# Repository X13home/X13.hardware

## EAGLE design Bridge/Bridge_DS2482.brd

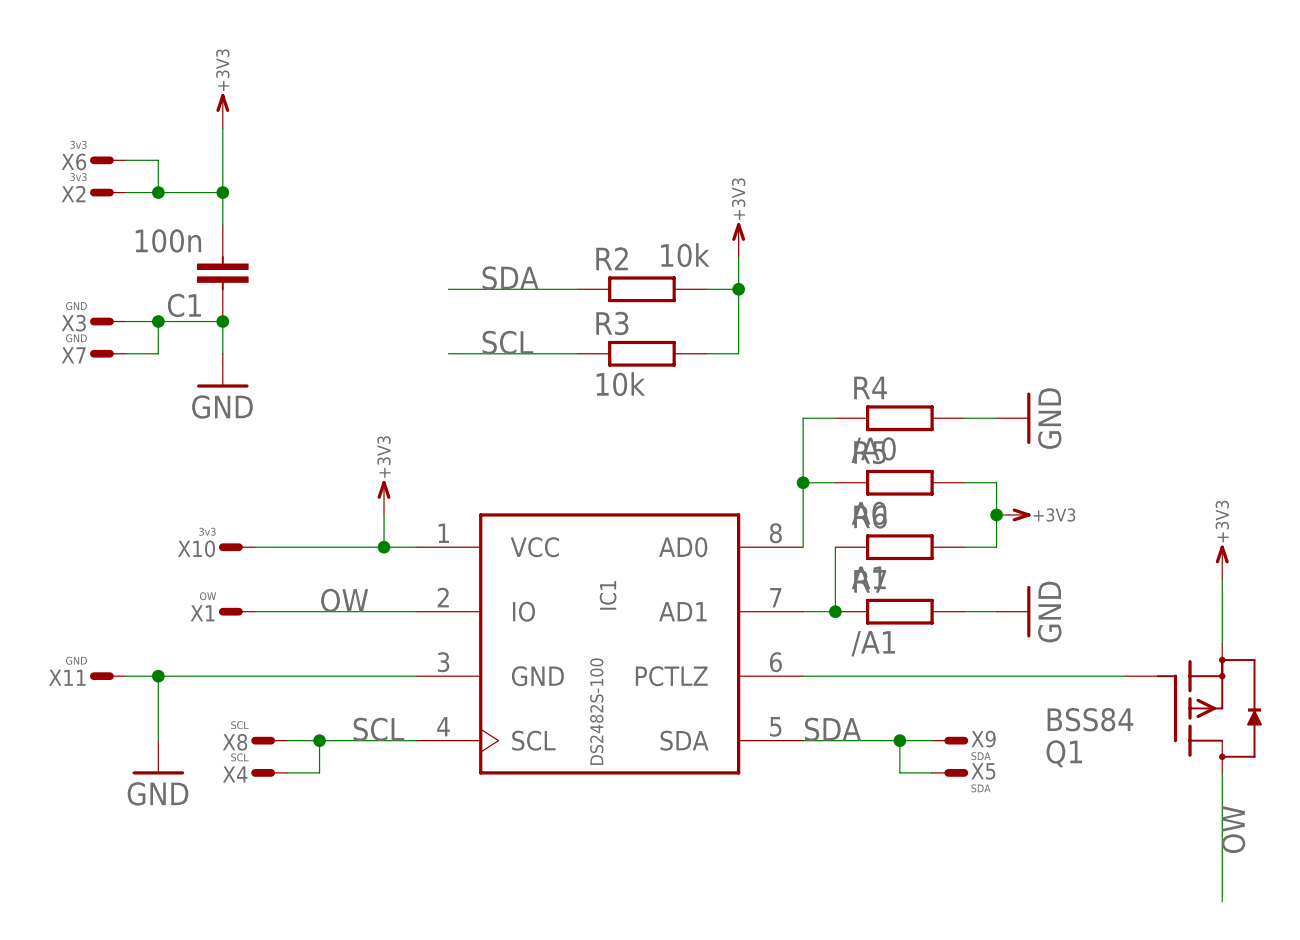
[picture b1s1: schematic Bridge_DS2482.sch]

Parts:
C1: 100n; 0603
IC1: DS2482S-100; SO8
Q1: BSS84; SOT23
R2, R3: 10k; 0603
R4: /A0; 0603
R5: A0; 0603
R6: A1; 0603
R7: /A1; 0603
X1: OW; T1.6/0.9
X2, X6, X10: 3v3; T1.6/0.9
X3, X7, X11: GND; T1.6/0.9
X4, X8: SCL; T1.6/0.9
X5, X9: SDA; T1.6/0.9

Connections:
+3V3: C1.2, IC1.1 (VCC), Q1.2 (S), R2.2, R3.2, R5.2, R6.2, X2.1, X6.1, X10.1
GND: C1.1, IC1.3 (GND), R4.2, R7.2, X3.1, X7.1, X11.1
unnamed: IC1.7 (AD1), R6.1, R7.1
unnamed: IC1.8 (AD0), R4.1, R5.1
unnamed: IC1.6 (PCTLZ), Q1.1 (G)
OW: IC1.2 (IO), Q1.3 (D), X1.1
SCL: IC1.4 (SCL), R3.1, X4.1, X8.1
SDA: IC1.5 (SDA), R2.1, X5.1, X9.1

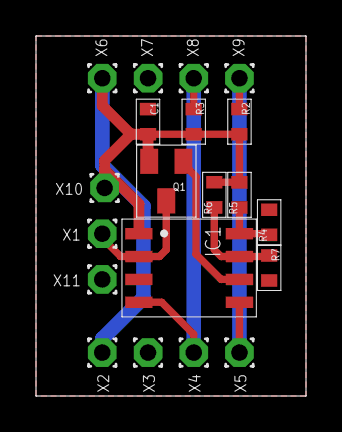
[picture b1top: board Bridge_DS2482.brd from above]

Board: 2 copper layers, 15.0 x 20.0 mm, 20 parts (0 on the bottom side), 8 nets.

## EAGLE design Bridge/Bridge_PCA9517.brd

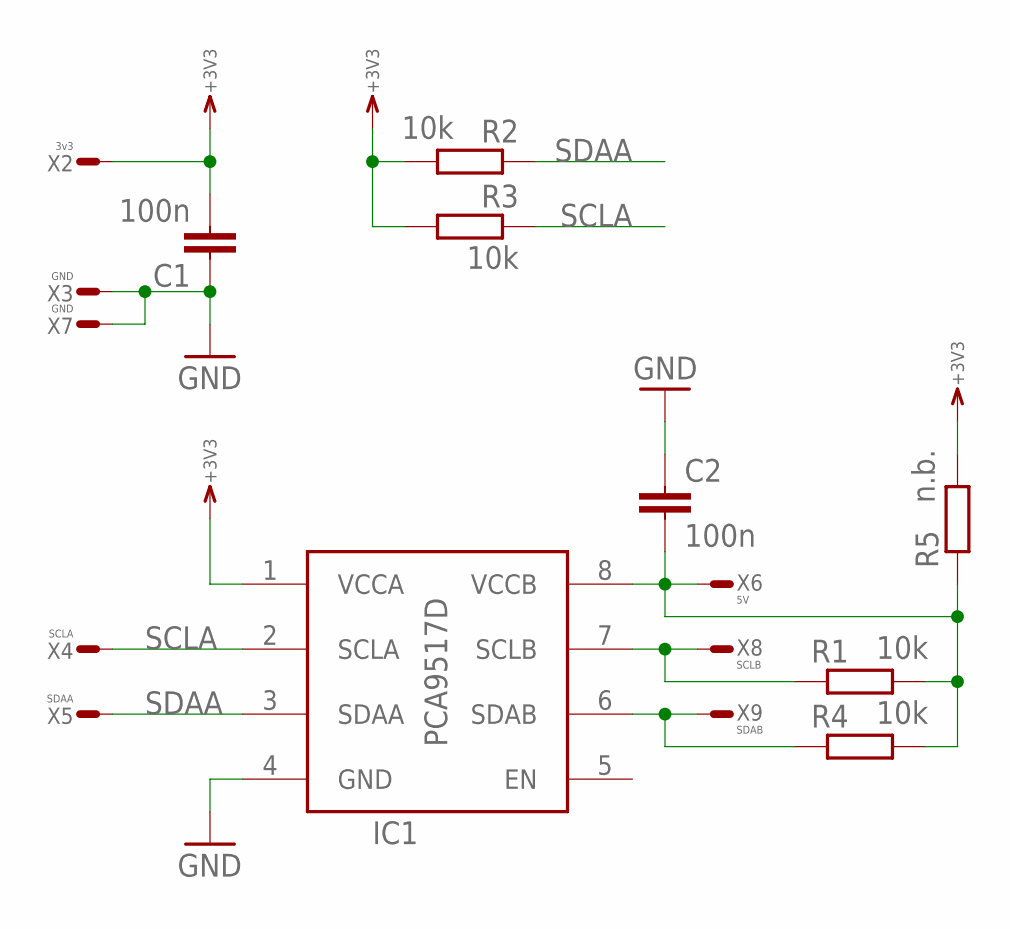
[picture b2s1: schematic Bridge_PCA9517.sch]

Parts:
C1, C2: 100n; 0603
IC1: PCA9517D; SOIC8
R1, R2, R3, R4: 10k; 0603
R5: n.b.; 0603
X2: 3v3; T1.6/0.9
X3, X7: GND; T1.6/0.9
X4: SCLA; T1.6/0.9
X5: SDAA; T1.6/0.9
X6: 5V; T1.6/0.9
X8: SCLB; T1.6/0.9
X9: SDAB; T1.6/0.9

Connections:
+3V3: C1.2, IC1.1 (VCCA), R2.2, R3.2, R5.2, X2.1
GND: C1.1, C2.1, IC1.4 (GND), X3.1, X7.1
unnamed: C2.2, IC1.8 (VCCB), R1.2, R4.2, R5.1, X6.1
SCLA: IC1.2 (SCLA), R3.1, X4.1
SCLB: IC1.7 (SCLB), R1.1, X8.1
SDAA: IC1.3 (SDAA), R2.1, X5.1
SDAB: IC1.6 (SDAB), R4.1, X9.1

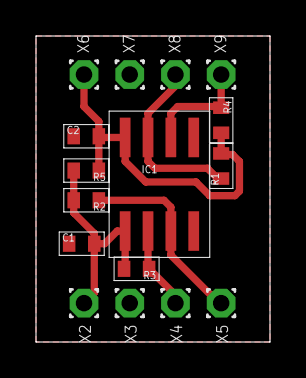
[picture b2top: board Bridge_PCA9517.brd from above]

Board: 2 copper layers, 13.0 x 17.0 mm, 16 parts (0 on the bottom side), 7 nets.

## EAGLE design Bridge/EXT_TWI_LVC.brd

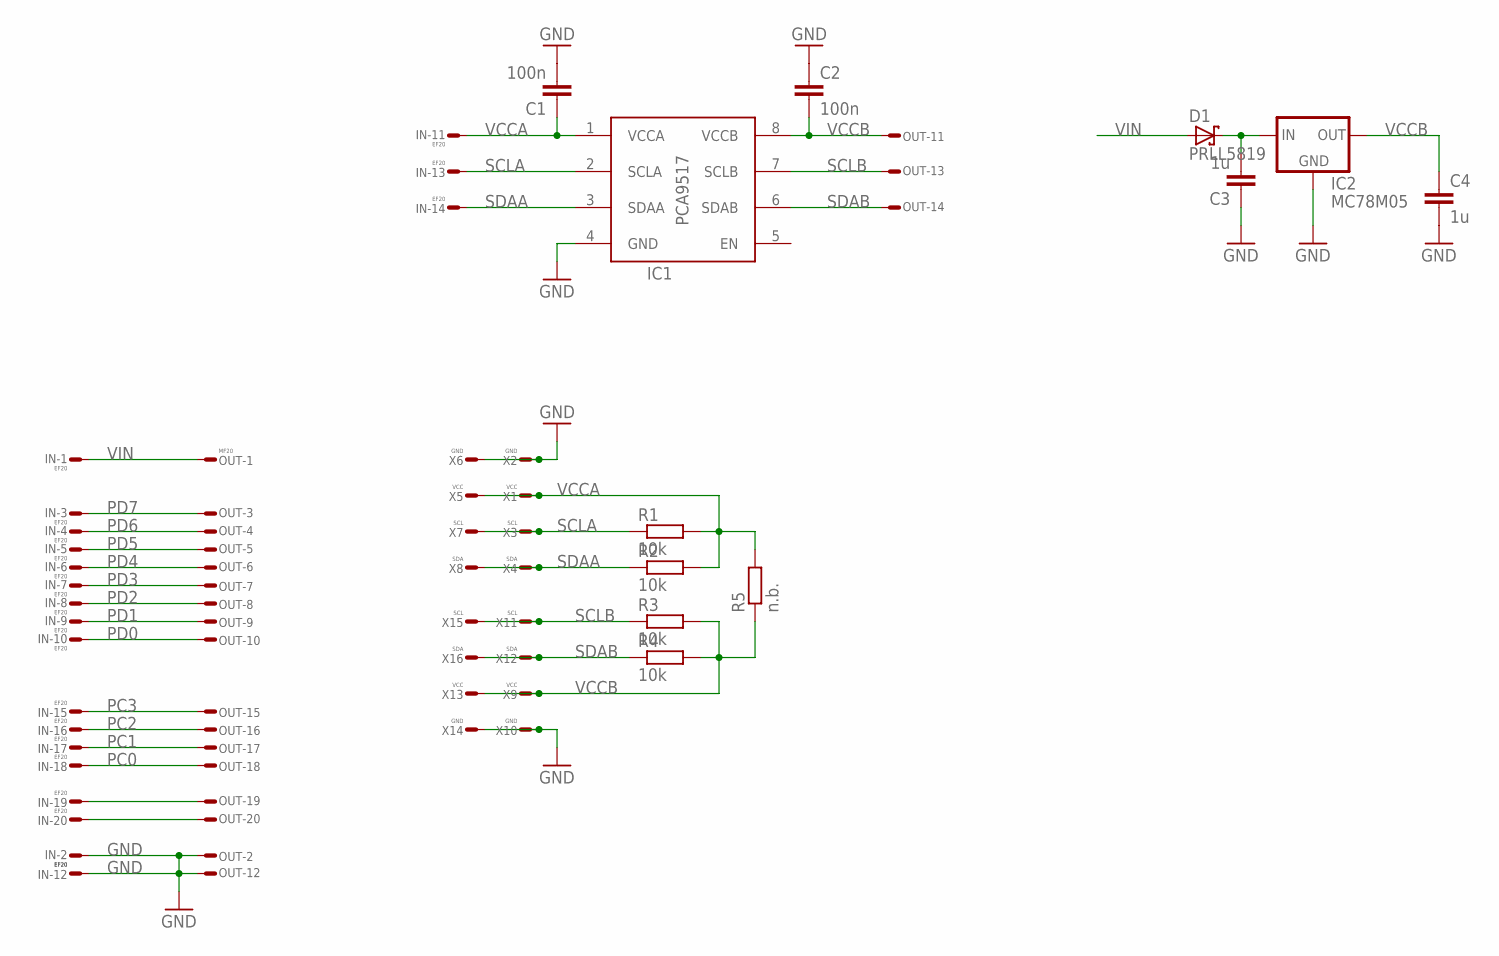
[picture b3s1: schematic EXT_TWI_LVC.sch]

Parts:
C1, C2: 100n; 0603
C3, C4: 1u; 1206
D1: PRLL5819; SOD87
IC1: PCA9517; SOIC8
IC2: MC78M05; DPAK
IN: EF20; FE10-2WSS
OUT: MF20; ML20LS
R1, R2, R3, R4: 10k; 0603
R5: n.b.; 1206
X1, X5, X9, X13: VCC; T1.6/0.9
X2, X6, X10, X14: GND; T1.6/0.9
X3, X7, X11, X15: SCL; T1.6/0.9
X4, X8, X12, X16: SDA; T1.6/0.9

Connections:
GND: C1.2, C2.1, C3.1, C4.2, IC1.4 (GND), IC2.4 (GND), IN.P$2, IN.P$12, OUT.P$2, OUT.P$12, X2.1, X6.1, X10.1, X14.1
unnamed: IN.P$20, OUT.P$20
unnamed: C3.2, D1.C, IC2.1 (IN)
unnamed: IN.P$19, OUT.P$19
PC0: IN.P$18, OUT.P$18
PC1: IN.P$17, OUT.P$17
PC2: IN.P$16, OUT.P$16
PC3: IN.P$15, OUT.P$15
PD0: IN.P$10, OUT.P$10
PD1: IN.P$9, OUT.P$9
PD2: IN.P$8, OUT.P$8
PD3: IN.P$7, OUT.P$7
PD4: IN.P$6, OUT.P$6
PD5: IN.P$5, OUT.P$5
PD6: IN.P$4, OUT.P$4
PD7: IN.P$3, OUT.P$3
SCLA: IC1.2 (SCLA), IN.P$13, R1.1, X3.1, X7.1
SCLB: IC1.7 (SCLB), OUT.P$13, R3.1, X11.1, X15.1
SDAA: IC1.3 (SDAA), IN.P$14, R2.1, X4.1, X8.1
SDAB: IC1.6 (SDAB), OUT.P$14, R4.1, X12.1, X16.1
VCCA: C1.1, IC1.1 (VCCA), IN.P$11, R1.2, R2.2, R5.2, X1.1, X5.1
VCCB: C2.2, C4.1, IC1.8 (VCCB), IC2.3 (OUT), OUT.P$11, R3.2, R4.2, R5.1, X9.1, X13.1
VIN: D1.A, IN.P$1, OUT.P$1

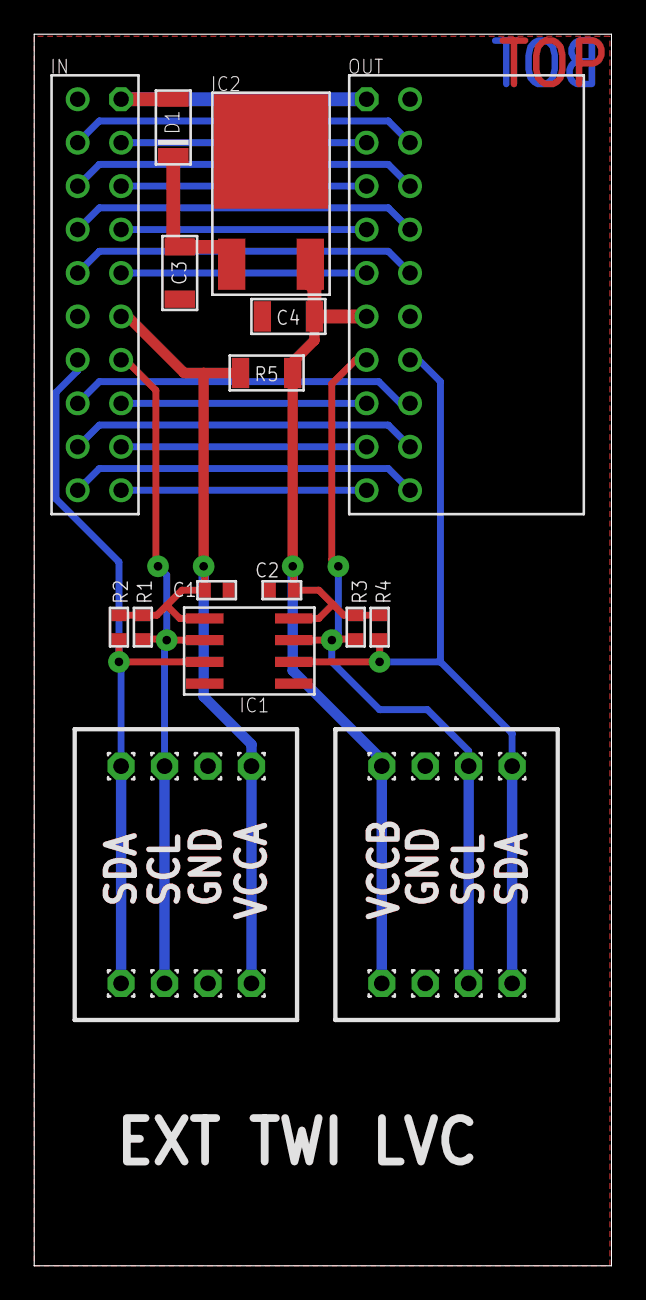
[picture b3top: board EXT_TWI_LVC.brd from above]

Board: 2 copper layers, 33.8 x 72.0 mm, 30 parts (0 on the bottom side), 23 nets.

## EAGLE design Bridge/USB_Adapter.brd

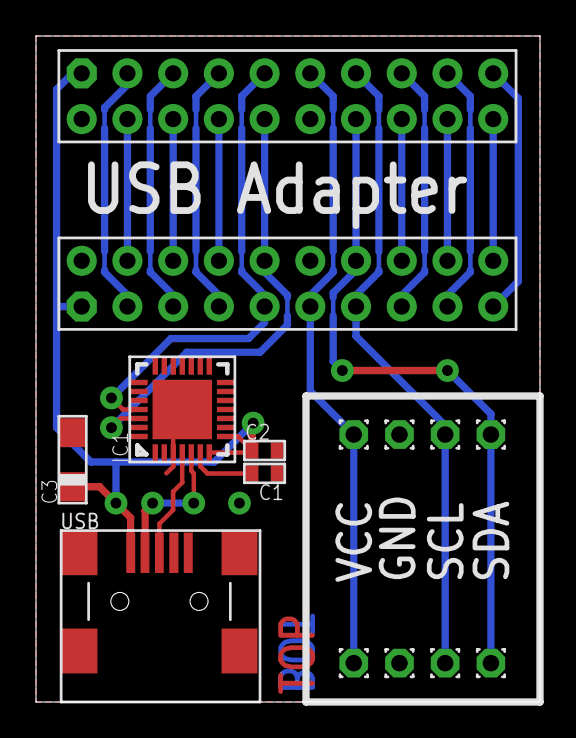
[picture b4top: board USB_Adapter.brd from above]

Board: 4 copper layers, 28.0 x 37.0 mm, 15 parts (1 on the bottom side), 22 nets.

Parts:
C1: 100n; 0603
C2: 1u; 0603
C3: 4u7; SMC_A
IC1: QFN28
OUT: MF20; ML20S
TRV: ML20S
USB: USB-BM
X1, X3, X4, X5, X6, X7, X8, X9: T1.6/0.9

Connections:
+3V3: OUT.11, TRV.11, X1.1, X6.1
GND: C1.1, C2.2, C3.-, IC1.3, IC1.P, OUT.2, OUT.12, TRV.2, TRV.12, USB.5, X3.1, X7.1
unnamed: OUT.20, TRV.20
unnamed: C1.2, IC1.6
unnamed: OUT.19, TRV.19
unnamed: IC1.4, USB.3
unnamed: IC1.5, USB.2
PC0: OUT.18, TRV.18
PC1: OUT.17, TRV.17
PC2: OUT.16, TRV.16
PC3: OUT.15, TRV.15
PC4/SDA: OUT.14, TRV.14, X5.1, X9.1
PC5/SCL: OUT.13, TRV.13, X4.1, X8.1
PD0: IC1.26, OUT.10, TRV.10
PD1: IC1.25, OUT.9, TRV.9
PD2: OUT.8, TRV.8
PD3: OUT.7, TRV.7
PD4: OUT.6, TRV.6
PD5: OUT.5, TRV.5
PD6: OUT.4, TRV.4
PD7: OUT.3, TRV.3
VIN: C2.1, C3.+, IC1.7, IC1.8, OUT.1, TRV.1, USB.1

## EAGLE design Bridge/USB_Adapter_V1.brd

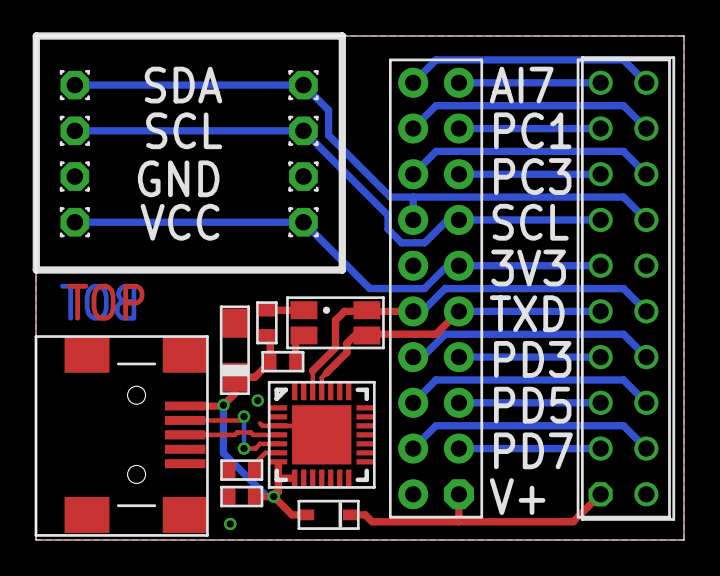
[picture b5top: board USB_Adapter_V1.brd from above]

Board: 2 copper layers, 36.0 x 28.0 mm, 19 parts (0 on the bottom side), 25 nets.

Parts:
C1: 100n; 0603
C2: 1u; 0603
C3: 4u7; SMC_A
D1: SOD323
IC1: CP2102; QFN28
LED1: HSMF
R1, R2: 1K; 0603
SV1: TRV; FE10-2WSS
SV2: ML20S
USB: USB; USB-BM
X1, X3, X4, X5, X6, X7, X8, X9: T1.6/0.9

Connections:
+3V3: SV1.P$11, SV2.11, X1.1, X6.1
AI6: SV1.P$20, SV2.20
AI7: SV1.P$19, SV2.19
GND: C1.1, C2.2, C3.-, IC1.3, IC1.P, SV1.P$2, SV1.P$12, SV2.2, SV2.12, USB.5, X3.1, X7.1
unnamed: D1.C, SV1.P$1, SV2.1
unnamed: C1.2, IC1.6
unnamed: LED1.3, R1.1
unnamed: IC1.4, USB.3
unnamed: LED1.1, R2.1
unnamed: IC1.5, USB.2
PC0: SV1.P$18, SV2.18
PC1: SV1.P$17, SV2.17
PC2: SV1.P$16, SV2.16
PC3: SV1.P$15, SV2.15
PC4/SDA: SV1.P$14, SV2.14, X5.1, X9.1
PC5/SCL: SV1.P$13, SV2.13, X4.1, X8.1
PD0: IC1.26, LED1.2, SV1.P$10, SV2.10
PD1: IC1.25, LED1.4, SV1.P$9, SV2.9
PD2: SV1.P$8, SV2.8
PD3: SV1.P$7, SV2.7
PD4: SV1.P$6, SV2.6
PD5: SV1.P$5, SV2.5
PD6: SV1.P$4, SV2.4
PD7: SV1.P$3, SV2.3
VIN: C2.1, C3.+, D1.A, IC1.7, IC1.8, R1.2, R2.2, USB.1

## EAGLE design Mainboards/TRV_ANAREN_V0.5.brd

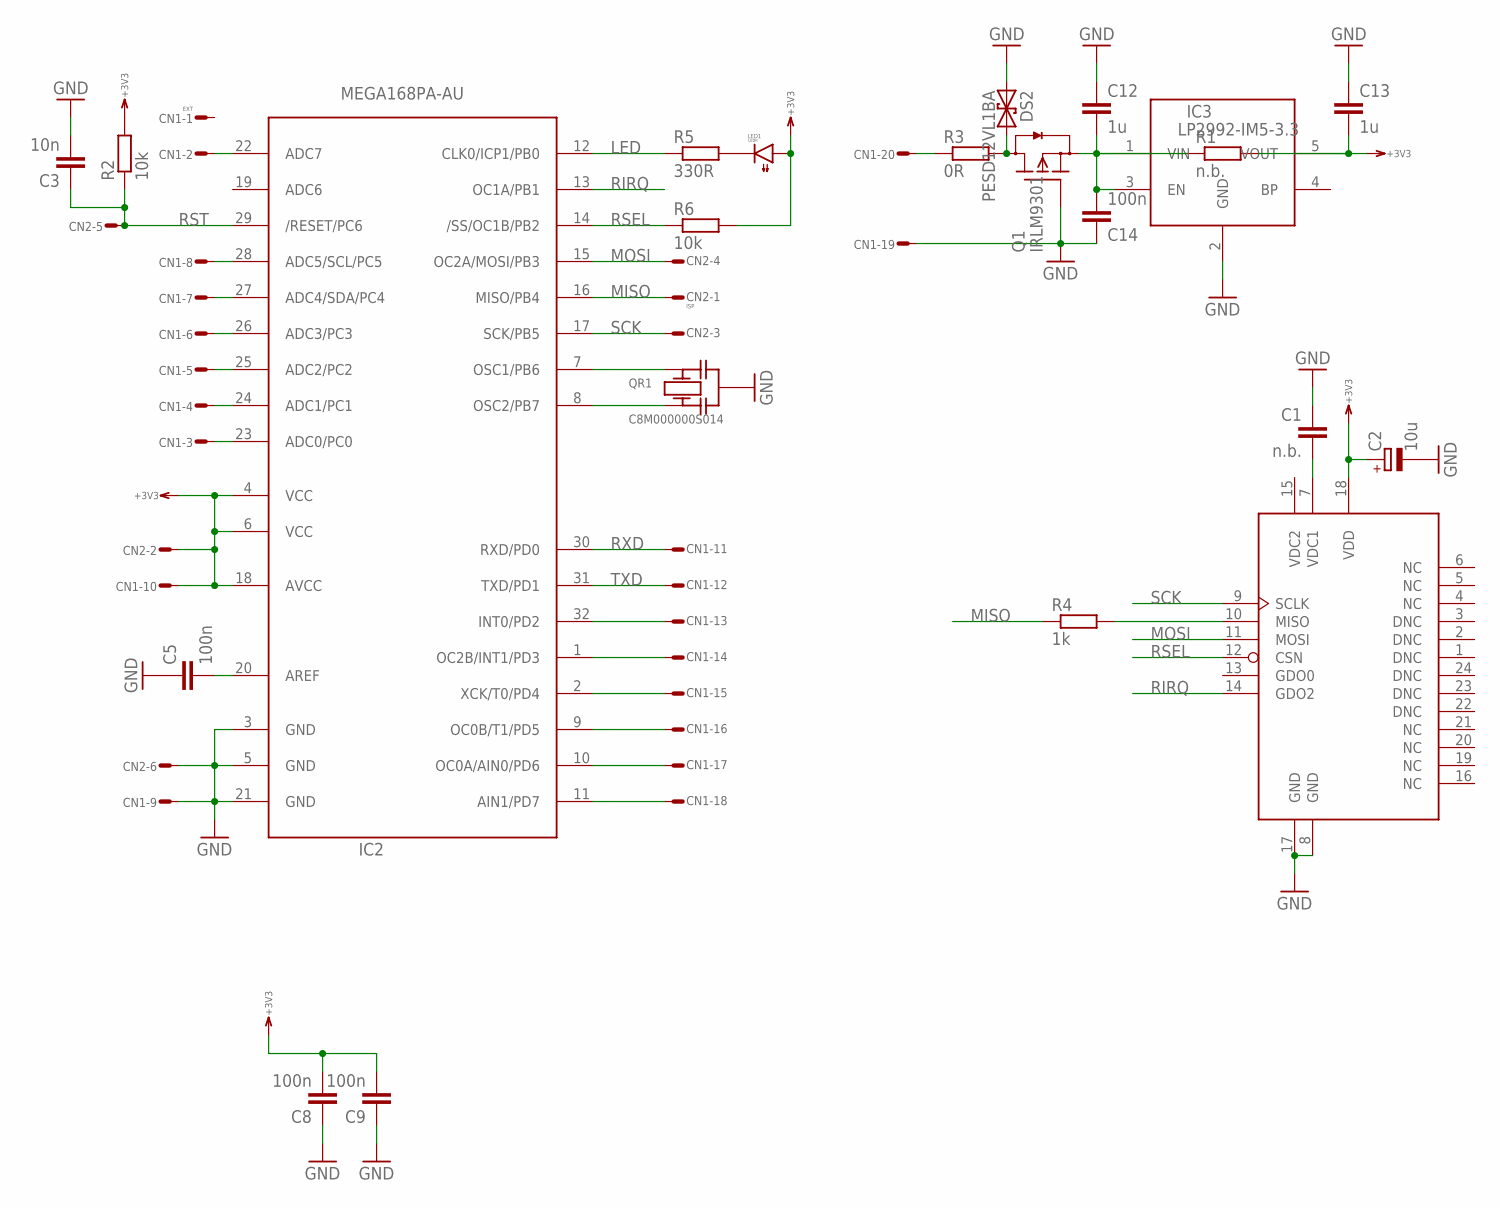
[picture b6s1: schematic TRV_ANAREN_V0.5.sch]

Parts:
C1: n.b.; 0603
C2: 10u; SMC_B
C3: 10n; 0603
C5, C8, C9, C14: 100n; 0603
C12, C13: 1u; 0603
CN1: EXT; ML20S
CN2: ISP; ML6S
DS2: PESD12VL1BA; SOD323
IC2: MEGA168PA-AU; TQFP32-08
IC3: LP2992-IM5-3.3; SOT23-5
LED1: LEDR; 0603
Q1: IRLM9301; SOT23
QR1: C8M000000S014; CR
R1: n.b.; 0603
R2, R6: 10k; 0603
R3: 0R; 0603
R4: 1k; 0603
R5: 330R; 0603
RF1: ANARENC; ANAREN_C

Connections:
+3V3: C2.+, C8.2, C9.2, C13.2, CN1.10, CN2.2, IC2.4 (VCC), IC2.6 (VCC), IC2.18 (AVCC), IC3.5 (VOUT), LED1.1 (A), R1.2, R2.2, R6.2, RF1.18 (VDD)
GND: C1.1, C2.-, C3.2, C5.1, C8.1, C9.1, C12.1, C13.1, C14.1, CN1.9, CN1.19, CN2.6, DS2.A (1), IC2.3 (GND), IC2.5 (GND), IC2.21 (GND), IC3.2 (GND), Q1.1 (G), QR1.M, RF1.8 (GND), RF1.17 (GND)
LED: IC2.12 (CLK0/ICP1/PB0), R5.1
MISO: CN2.1, IC2.16 (MISO/PB4), R4.1
MOSI: CN2.4, IC2.15 (OC2A/MOSI/PB3), RF1.11 (MOSI)
unnamed: C1.2, RF1.7 (VDC1)
unnamed: R4.2, RF1.10 (MISO)
unnamed: CN1.2, IC2.22 (ADC7)
unnamed: DS2.C (2), Q1.3 (D), R3.2
unnamed: C5.2, IC2.20 (AREF)
unnamed: C12.2, C14.2, IC3.1 (VIN), IC3.3 (EN), Q1.2 (S), R1.1
unnamed: IC2.7 (OSC1/PB6), QR1.2
unnamed: IC2.8 (OSC2/PB7), QR1.1
unnamed: LED1.2 (C), R5.2
PC0: CN1.3, IC2.23 (ADC0/PC0)
PC1: CN1.4, IC2.24 (ADC1/PC1)
PC2: CN1.5, IC2.25 (ADC2/PC2)
PC3: CN1.6, IC2.26 (ADC3/PC3)
PC4: CN1.7, IC2.27 (ADC4/SDA/PC4)
PC5: CN1.8, IC2.28 (ADC5/SCL/PC5)
PD2: CN1.13, IC2.32 (INT0/PD2)
PD3: CN1.14, IC2.1 (OC2B/INT1/PD3)
PD4: CN1.15, IC2.2 (XCK/T0/PD4)
PD5: CN1.16, IC2.9 (OC0B/T1/PD5)
PD6: CN1.17, IC2.10 (OC0A/AIN0/PD6)
PD7: CN1.18, IC2.11 (AIN1/PD7)
RIRQ: IC2.13 (OC1A/PB1), RF1.14 (GDO2)
RSEL: IC2.14 (/SS/OC1B/PB2), R6.1, RF1.12 (CSN)
RST: C3.1, CN2.5, IC2.29 (/RESET/PC6), R2.1
RXD: CN1.11, IC2.30 (RXD/PD0)
SCK: CN2.3, IC2.17 (SCK/PB5), RF1.9 (SCLK)
TXD: CN1.12, IC2.31 (TXD/PD1)
VIN: CN1.20, R3.1

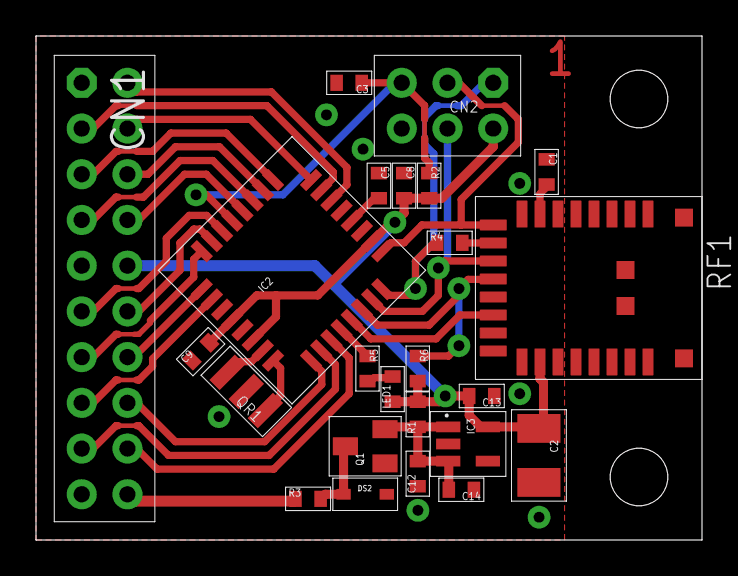
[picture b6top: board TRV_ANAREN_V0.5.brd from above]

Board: 2 copper layers, 37.0 x 28.0 mm, 24 parts (0 on the bottom side), 33 nets.

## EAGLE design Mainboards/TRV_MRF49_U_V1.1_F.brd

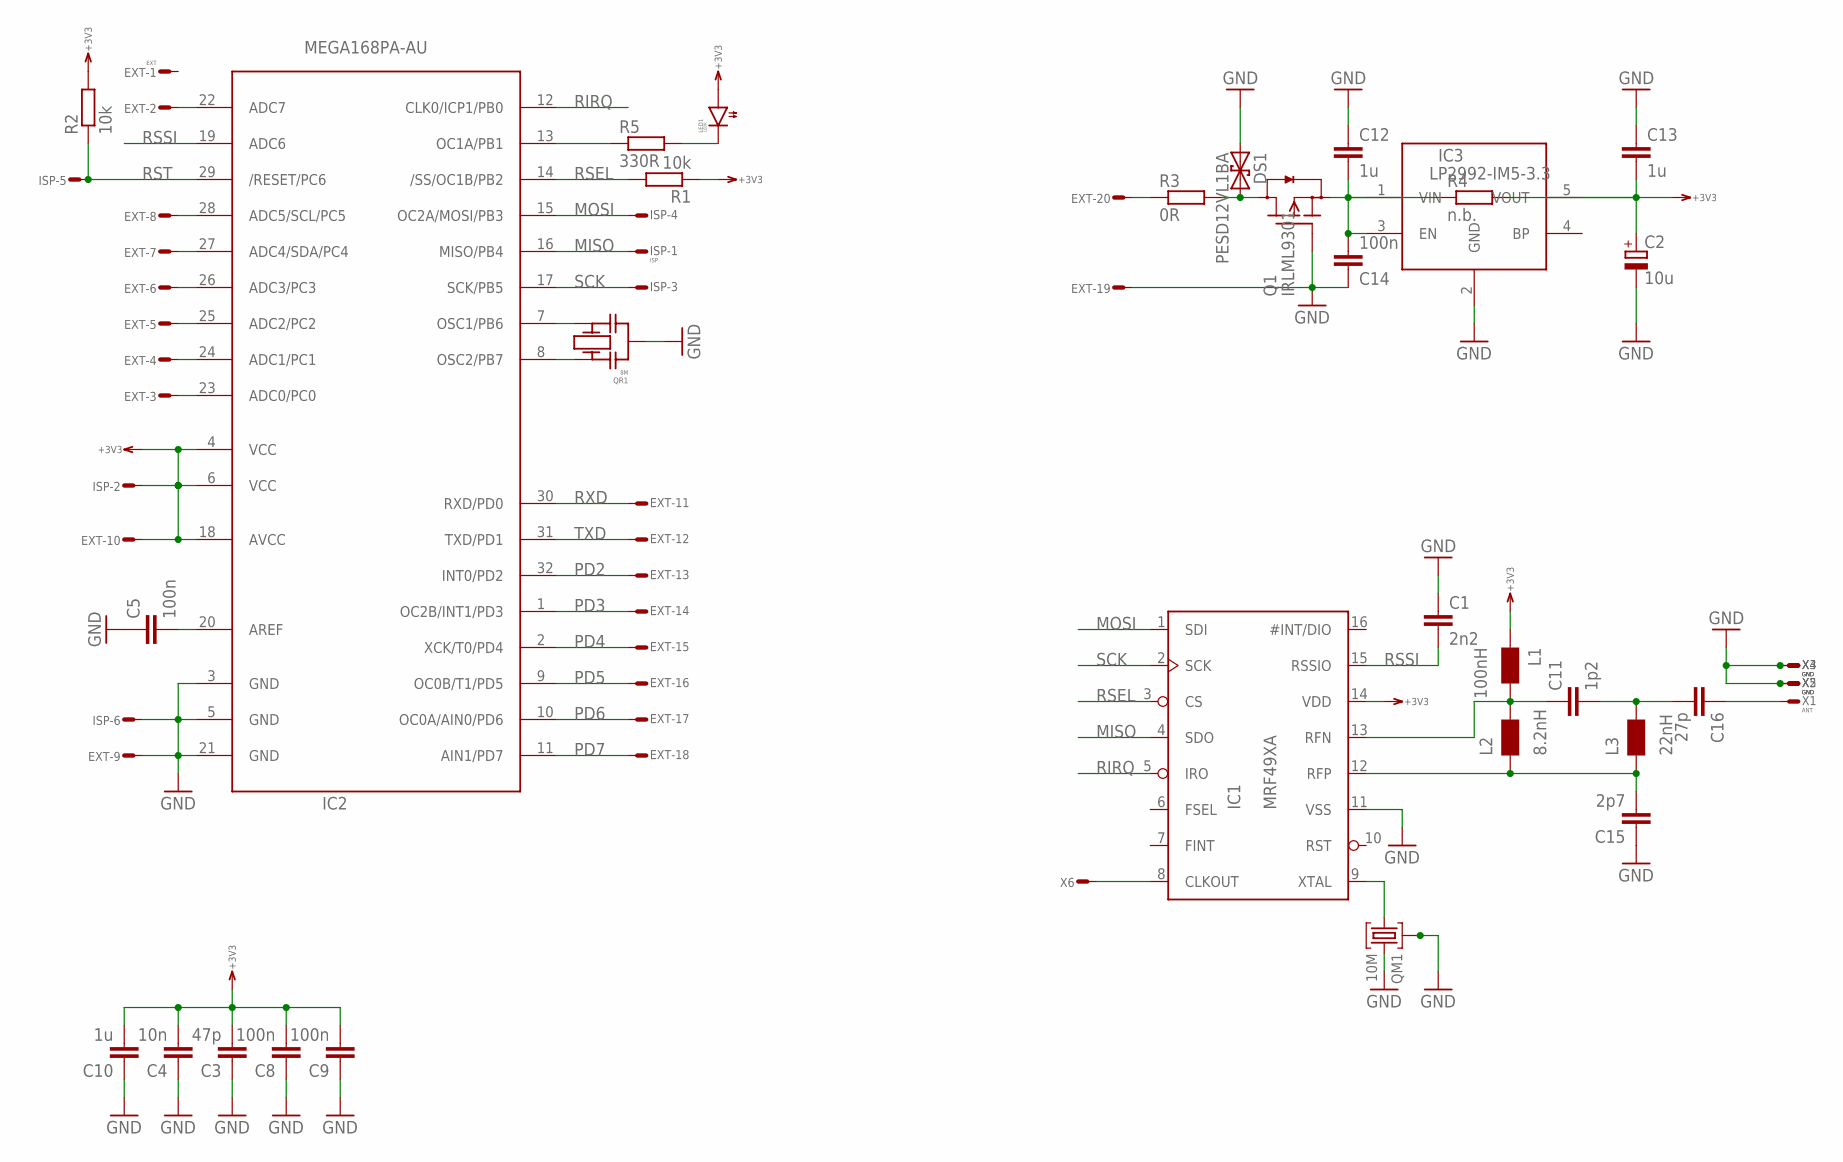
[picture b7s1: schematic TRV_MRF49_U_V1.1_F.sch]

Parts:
C1: 2n2; 0603
C2: 10u; SMC_B
C3: 47p; 0603
C4: 10n; 0603
C5, C8, C9, C14: 100n; 0603
C10, C12, C13: 1u; 0603
C11: 1p2; 0603
C15: 2p7; 0603
C16: 27p; 0603
DS1: PESD12VL1BA; SOD323
EXT: EXT; ML20S
IC1: MRF49XA; TSSOP16
IC2: MEGA168PA-AU; TQFP32-08
IC3: LP2992-IM5-3.3; SOT23-5
ISP: ISP; ML6S
L1: 100nH; 0603
L2: 8.2nH; 0603
L3: 22nH; 0603
LED1: LEDR; 0603
Q1: IRLML9301; SOT23
QM1: 10M; ABM3C
QR1: 8M; CR
R1, R2: 10k; 0603
R3: 0R; 0603
R4: n.b.; 0603
R5: 330R; 0603
X1: ANT; S2.54/1.27
X2, X3, X4, X5: GND; S2.54/1.27
X6: WIREPADR; S1.27R

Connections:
+3V3: C2.+, C3.2, C4.2, C8.2, C9.2, C10.2, C13.2, EXT.10, IC1.14 (VDD), IC2.4 (VCC), IC2.6 (VCC), IC2.18 (AVCC), IC3.5 (VOUT), ISP.2, L1.1, LED1.1 (A), R1.1, R2.2, R4.2
GND: C1.1, C2.-, C3.1, C4.1, C5.1, C8.1, C9.1, C10.1, C12.1, C13.1, C14.1, C15.1, DS1.A (1), EXT.9, EXT.19, IC1.11 (VSS), IC2.3 (GND), IC2.5 (GND), IC2.21 (GND), IC3.2 (GND), ISP.6, Q1.1 (G), QM1.P$2 (M1), QM1.P$3 (2), QM1.P$4 (M2), QR1.M, X2.1, X3.1, X4.1, X5.1
MISO: IC1.4 (SDO), IC2.16 (MISO/PB4), ISP.1
MOSI: IC1.1 (SDI), IC2.15 (OC2A/MOSI/PB3), ISP.4
unnamed: IC1.8 (CLKOUT), X6.1
unnamed: C11.2, C16.2, L3.2
unnamed: EXT.2, IC2.22 (ADC7)
unnamed: IC1.9 (XTAL), QM1.P$1 (1)
unnamed: DS1.C (2), Q1.3 (D), R3.2
unnamed: C5.2, IC2.20 (AREF)
unnamed: IC2.8 (OSC2/PB7), QR1.1
unnamed: IC2.7 (OSC1/PB6), QR1.2
unnamed: EXT.20, R3.1
unnamed: IC2.13 (OC1A/PB1), R5.1
unnamed: C12.2, C14.2, IC3.1 (VIN), IC3.3 (EN), Q1.2 (S), R4.1
unnamed: C11.1, IC1.13 (RFN), L1.2, L2.2
unnamed: LED1.2 (C), R5.2
unnamed: C15.2, IC1.12 (RFP), L2.1, L3.1
unnamed: C16.1, X1.1
PC0: EXT.3, IC2.23 (ADC0/PC0)
PC1: EXT.4, IC2.24 (ADC1/PC1)
PC2: EXT.5, IC2.25 (ADC2/PC2)
PC3: EXT.6, IC2.26 (ADC3/PC3)
PC4: EXT.7, IC2.27 (ADC4/SDA/PC4)
PC5: EXT.8, IC2.28 (ADC5/SCL/PC5)
PD2: EXT.13, IC2.32 (INT0/PD2)
PD3: EXT.14, IC2.1 (OC2B/INT1/PD3)
PD4: EXT.15, IC2.2 (XCK/T0/PD4)
PD5: EXT.16, IC2.9 (OC0B/T1/PD5)
PD6: EXT.17, IC2.10 (OC0A/AIN0/PD6)
PD7: EXT.18, IC2.11 (AIN1/PD7)
RIRQ: IC1.5 (IRO), IC2.12 (CLK0/ICP1/PB0)
RSEL: IC1.3 (CS), IC2.14 (/SS/OC1B/PB2), R1.2
RSSI: C1.2, IC1.15 (RSSIO), IC2.19 (ADC6)
RST: IC2.29 (/RESET/PC6), ISP.5, R2.1
RXD: EXT.11, IC2.30 (RXD/PD0)
SCK: IC1.2 (SCK), IC2.17 (SCK/PB5), ISP.3
TXD: EXT.12, IC2.31 (TXD/PD1)

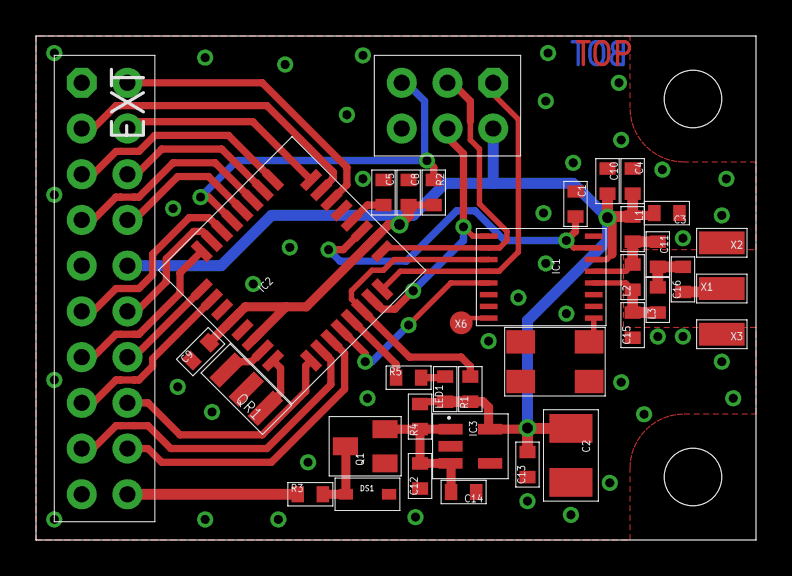
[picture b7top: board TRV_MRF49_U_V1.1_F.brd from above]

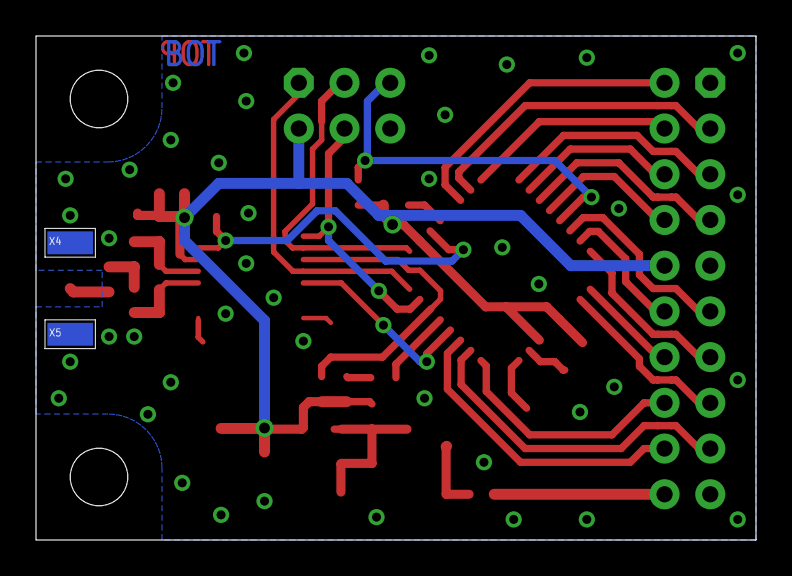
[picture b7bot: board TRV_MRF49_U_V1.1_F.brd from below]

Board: 2 copper layers, 40.0 x 28.0 mm, 38 parts (2 on the bottom side), 38 nets.
